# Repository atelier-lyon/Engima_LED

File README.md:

# Enigma Led

## By Florian "FloRide" Reimat

## About

This repo is the LED panel PCB of the Enigma project

## Images:

### Schematic:

### PCB:

|              Front               |               Bottom               |
| :------------------------------: | :--------------------------------: |
|  |  |

### 3D:

|                Front                 |                Bottom                |
| :----------------------------------: | :----------------------------------: |
|    |  |
|               Tilted 1               |               Tilted 2               |
|  |   |

## Others:

- [Interactive BOM](Export/ibom/Engima_LED-ibom.html)
- [BOM](Export/bom/Engima_LED-bom.csv)
- [Cost](Export/cost/Engima_LED-kicost.xlsx)

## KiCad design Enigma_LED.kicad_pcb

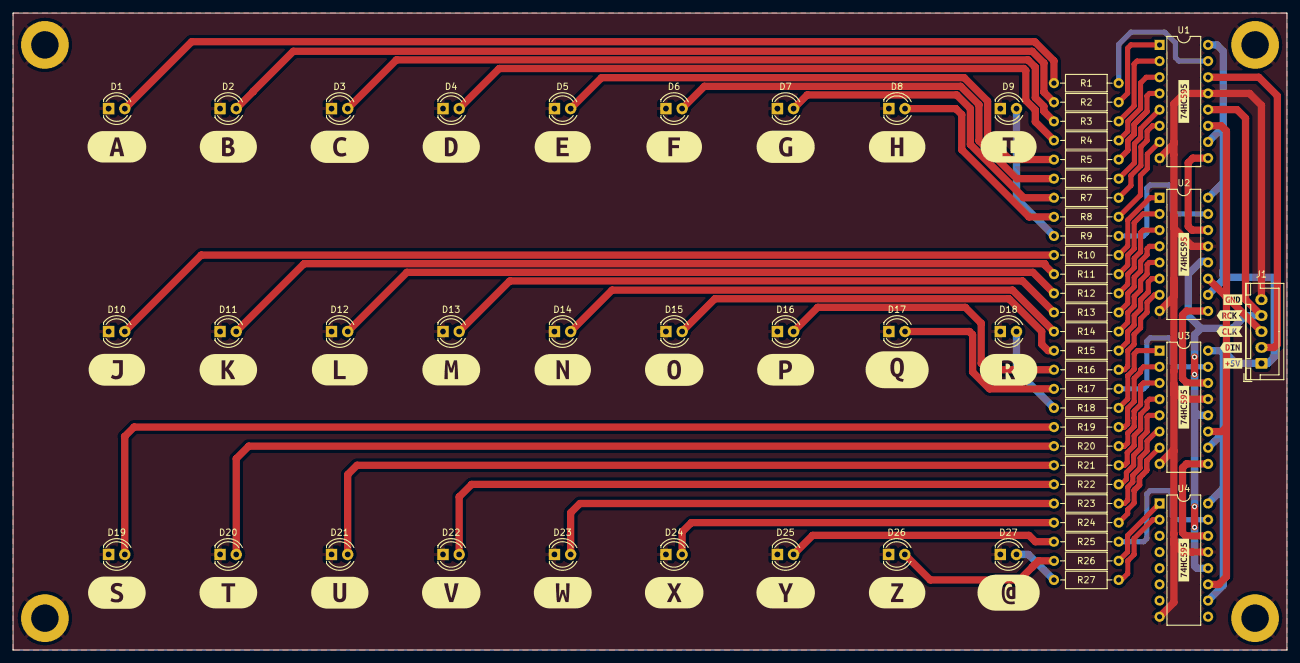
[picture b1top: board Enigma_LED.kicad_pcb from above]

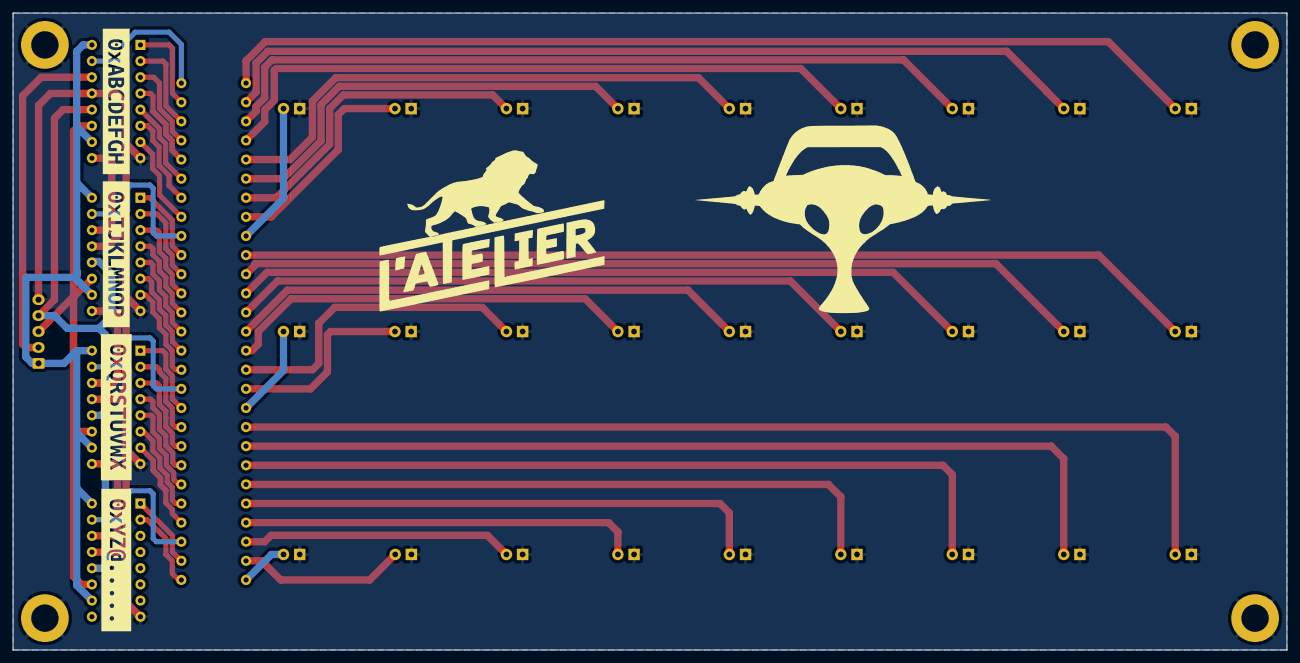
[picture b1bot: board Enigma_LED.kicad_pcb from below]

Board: 2 copper layers, 200.0 x 100.0 mm, 103 parts (4 on the bottom side), 62 nets.

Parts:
D1: LED_A; LED_D4.0mm
D2: LED_B; LED_D4.0mm
D3: LED_C; LED_D4.0mm
D4: LED_D; LED_D4.0mm
D5: LED_E; LED_D4.0mm
D6: LED_F; LED_D4.0mm
D7: LED_G; LED_D4.0mm
D8: LED_H; LED_D4.0mm
D9: LED_I; LED_D4.0mm
D10: LED_J; LED_D4.0mm
D11: LED_K; LED_D4.0mm
D12: LED_L; LED_D4.0mm
D13: LED_M; LED_D4.0mm
D14: LED_N; LED_D4.0mm
D15: LED_O; LED_D4.0mm
D16: LED_P; LED_D4.0mm
D17: LED_Q; LED_D4.0mm
D18: LED_R; LED_D4.0mm
D19: LED_S; LED_D4.0mm
D20: LED_T; LED_D4.0mm
D21: LED_U; LED_D4.0mm
D22: LED_V; LED_D4.0mm
D23: LED_W; LED_D4.0mm
D24: LED_X; LED_D4.0mm
D25: LED_Y; LED_D4.0mm
D26: LED_Z; LED_D4.0mm
D27: LED_@; LED_D4.0mm
H1, H2, H3, H4: MountingHole_Pad; MountingHole_4.3mm_M4_DIN965_Pad
J1: Conn_01x05; JST_XH_B5B-XH-A_1x05_P2.50mm_Vertical
R1: R_A; R_Axial_DIN0207_L6.3mm_D2.5mm_P10.16mm_Horizontal
R2: R_B; R_Axial_DIN0207_L6.3mm_D2.5mm_P10.16mm_Horizontal
R3: R_C; R_Axial_DIN0207_L6.3mm_D2.5mm_P10.16mm_Horizontal
R4: R_D; R_Axial_DIN0207_L6.3mm_D2.5mm_P10.16mm_Horizontal
R5: R_E; R_Axial_DIN0207_L6.3mm_D2.5mm_P10.16mm_Horizontal
R6: R_F; R_Axial_DIN0207_L6.3mm_D2.5mm_P10.16mm_Horizontal
R7: R_G; R_Axial_DIN0207_L6.3mm_D2.5mm_P10.16mm_Horizontal
R8: R_H; R_Axial_DIN0207_L6.3mm_D2.5mm_P10.16mm_Horizontal
R9: R_I; R_Axial_DIN0207_L6.3mm_D2.5mm_P10.16mm_Horizontal
R10: R_J; R_Axial_DIN0207_L6.3mm_D2.5mm_P10.16mm_Horizontal
R11: R_K; R_Axial_DIN0207_L6.3mm_D2.5mm_P10.16mm_Horizontal
R12: R_L; R_Axial_DIN0207_L6.3mm_D2.5mm_P10.16mm_Horizontal
R13: R_M; R_Axial_DIN0207_L6.3mm_D2.5mm_P10.16mm_Horizontal
R14: R_N; R_Axial_DIN0207_L6.3mm_D2.5mm_P10.16mm_Horizontal
R15: R_O; R_Axial_DIN0207_L6.3mm_D2.5mm_P10.16mm_Horizontal
R16: R_P; R_Axial_DIN0207_L6.3mm_D2.5mm_P10.16mm_Horizontal
R17: R_Q; R_Axial_DIN0207_L6.3mm_D2.5mm_P10.16mm_Horizontal
R18: R_R; R_Axial_DIN0207_L6.3mm_D2.5mm_P10.16mm_Horizontal
R19: R_S; R_Axial_DIN0207_L6.3mm_D2.5mm_P10.16mm_Horizontal
R20: R_T; R_Axial_DIN0207_L6.3mm_D2.5mm_P10.16mm_Horizontal
R21: R_U; R_Axial_DIN0207_L6.3mm_D2.5mm_P10.16mm_Horizontal
R22: R_V; R_Axial_DIN0207_L6.3mm_D2.5mm_P10.16mm_Horizontal
R23: R_W; R_Axial_DIN0207_L6.3mm_D2.5mm_P10.16mm_Horizontal
R24: R_X; R_Axial_DIN0207_L6.3mm_D2.5mm_P10.16mm_Horizontal
R25: R_Y; R_Axial_DIN0207_L6.3mm_D2.5mm_P10.16mm_Horizontal
R26: R_Z; R_Axial_DIN0207_L6.3mm_D2.5mm_P10.16mm_Horizontal
R27: R_@; R_Axial_DIN0207_L6.3mm_D2.5mm_P10.16mm_Horizontal
U1, U2, U3, U4: 74HC595; DIP-16_W7.62mm
kibuzzard-6370F7DB: G***; kibuzzard-6370F7DB
kibuzzard-6370F8AD: G***; kibuzzard-6370F8AD
kibuzzard-6370F8C8: G***; kibuzzard-6370F8C8
kibuzzard-6370F8CE: G***; kibuzzard-6370F8CE
kibuzzard-6370F8D3: G***; kibuzzard-6370F8D3
kibuzzard-6370F8D8: G***; kibuzzard-6370F8D8
kibuzzard-6370FC4A: G***; kibuzzard-6370FC4A
kibuzzard-6370FC51: G***; kibuzzard-6370FC51
kibuzzard-6370FC63: G***; kibuzzard-6370FC63
kibuzzard-6370FD4C: G***; kibuzzard-6370FD4C
kibuzzard-6370FD6F: G***; kibuzzard-6370FD6F
kibuzzard-6370FD7B: G***; kibuzzard-6370FD7B
kibuzzard-6370FD7F: G***; kibuzzard-6370FD7F
kibuzzard-6370FD9A: G***; kibuzzard-6370FD9A
kibuzzard-6370FD51: G***; kibuzzard-6370FD51
kibuzzard-6370FD57: G***; kibuzzard-6370FD57
kibuzzard-6370FD67: G***; kibuzzard-6370FD67
kibuzzard-6370FD75: G***; kibuzzard-6370FD75
kibuzzard-6370FD86: G***; kibuzzard-6370FD86
kibuzzard-6370FD95: G***; kibuzzard-6370FD95
kibuzzard-6370FDA1: G***; kibuzzard-6370FDA1
kibuzzard-6370FDA7: G***; kibuzzard-6370FDA7
kibuzzard-6370FDAC: G***; kibuzzard-6370FDAC
kibuzzard-6370FDB1: G***; kibuzzard-6370FDB1
kibuzzard-6370FDB7: G***; kibuzzard-6370FDB7
kibuzzard-6370FDBC: G***; kibuzzard-6370FDBC
kibuzzard-6370FDCC: G***; kibuzzard-6370FDCC
kibuzzard-6370FEE8, kibuzzard-6370FEE8#2, kibuzzard-6370FEE8#3, kibuzzard-6370FEE8#4: G***; kibuzzard-6370FEE8
kibuzzard-63715FEB: G***; kibuzzard-63715FEB
kibuzzard-63715FF9: G***; kibuzzard-63715FF9
kibuzzard-637101DC: G***; kibuzzard-637101DC
kibuzzard-6371013A: G***; kibuzzard-6371013A
kibuzzard-6371601F: G***; kibuzzard-6371601F
kibuzzard-63710104: G***; kibuzzard-63710104
kibuzzard-63710126: G***; kibuzzard-63710126
kibuzzard-63716000: G***; kibuzzard-63716000
kibuzzard-63716017: G***; kibuzzard-63716017

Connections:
+5V: J1.1, U1.10 (~SRCLR), U1.16 (VCC), U2.10 (~SRCLR), U2.16 (VCC), U3.10 (~SRCLR), U3.16 (VCC), U4.10 (~SRCLR), U4.16 (VCC)
/OUTPUT_@: R27.2, U4.2 (QC)
/OUTPUT_A: R1.2, U1.15 (QA)
/OUTPUT_B: R2.2, U1.1 (QB)
/OUTPUT_C: R3.2, U1.2 (QC)
/OUTPUT_D: R4.2, U1.3 (QD)
/OUTPUT_E: R5.2, U1.4 (QE)
/OUTPUT_F: R6.2, U1.5 (QF)
/OUTPUT_G: R7.2, U1.6 (QG)
/OUTPUT_H: R8.2, U1.7 (QH)
/OUTPUT_I: R9.2, U2.15 (QA)
/OUTPUT_J: R10.2, U2.1 (QB)
/OUTPUT_K: R11.2, U2.2 (QC)
/OUTPUT_L: R12.2, U2.3 (QD)
/OUTPUT_M: R13.2, U2.4 (QE)
/OUTPUT_N: R14.2, U2.5 (QF)
/OUTPUT_O: R15.2, U2.6 (QG)
/OUTPUT_P: R16.2, U2.7 (QH)
/OUTPUT_Q: R17.2, U3.15 (QA)
/OUTPUT_R: R18.2, U3.1 (QB)
/OUTPUT_S: R19.2, U3.2 (QC)
/OUTPUT_T: R20.2, U3.3 (QD)
/OUTPUT_U: R21.2, U3.4 (QE)
/OUTPUT_V: R22.2, U3.5 (QF)
/OUTPUT_W: R23.2, U3.6 (QG)
/OUTPUT_X: R24.2, U3.7 (QH)
/OUTPUT_Y: R25.2, U4.15 (QA)
/OUTPUT_Z: R26.2, U4.1 (QB)
GND: D1.1 (K), D2.1 (K), D3.1 (K), D4.1 (K), D5.1 (K), D6.1 (K), D7.1 (K), D8.1 (K), D9.1 (K), D10.1 (K), D11.1 (K), D12.1 (K), D13.1 (K), D14.1 (K), D15.1 (K), D16.1 (K), D17.1 (K), D18.1 (K), D19.1 (K), D20.1 (K), D21.1 (K), D22.1 (K), D23.1 (K), D24.1 (K), D25.1 (K), D26.1 (K), D27.1 (K), H1.1, H2.1, H3.1, H4.1, J1.5, U1.8 (GND), U1.13 (~OE), U2.8 (GND), U2.13 (~OE), U3.8 (GND), U3.13 (~OE), U4.8 (GND), U4.13 (~OE)
unnamed: D1.2 (A), R1.1
unnamed: D2.2 (A), R2.1
unnamed: D3.2 (A), R3.1
unnamed: D4.2 (A), R4.1
unnamed: D5.2 (A), R5.1
unnamed: D6.2 (A), R6.1
unnamed: D7.2 (A), R7.1
unnamed: D8.2 (A), R8.1
unnamed: D9.2 (A), R9.1
unnamed: D10.2 (A), R10.1
unnamed: D11.2 (A), R11.1
unnamed: D12.2 (A), R12.1
unnamed: D13.2 (A), R13.1
unnamed: D14.2 (A), R14.1
unnamed: D15.2 (A), R15.1
unnamed: D16.2 (A), R16.1
unnamed: D17.2 (A), R17.1
unnamed: D18.2 (A), R18.1
unnamed: D19.2 (A), R19.1
unnamed: D20.2 (A), R20.1
unnamed: D21.2 (A), R21.1
unnamed: D22.2 (A), R22.1
unnamed: D23.2 (A), R23.1
unnamed: D24.2 (A), R24.1
unnamed: D25.2 (A), R25.1
unnamed: D26.2 (A), R26.1
unnamed: D27.2 (A), R27.1
unnamed: U1.9 (QH'), U2.14 (SER)
unnamed: U2.9 (QH'), U3.14 (SER)
unnamed: U3.9 (QH'), U4.14 (SER)
OUTPUT_CLK: J1.3, U1.11 (SRCLK), U2.11 (SRCLK), U3.11 (SRCLK), U4.11 (SRCLK)
OUTPUT_DIN: J1.2, U1.14 (SER)
OUTPUT_RCK: J1.4, U1.12 (RCLK), U2.12 (RCLK), U3.12 (RCLK), U4.12 (RCLK)

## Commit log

2022-11-15 [ROOT] Initial commit
2022-11-15 [PRO][SCH][PCB] Add Kicad files
2022-11-15 [CI/CD] Add Kibot + CI/CD
2022-11-15 [CI/CD] Trigger CI run
2022-11-15 [ROOT] Fix typo in README
2023-01-25 [PCB] Small change in pcb
